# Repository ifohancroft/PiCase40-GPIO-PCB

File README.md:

Pi Case 40 GPIO PCB
===================

A replacement PCB (and a GPIO sticker) for the Pi Case 40, that fixes the reversed GPIO Issue.

 - The PCB can be located under PiCase40/. It includes all the schematic symbols, footprints and 3D shapes it uses, in project-specific libraries, located under Library/.
 - sticker.svg is the GPIO sticker.
 - PCBReference.FCStd contains the PCB dimensions and component placements, as well as technical drawings for all the important size and space restrictions that need to be taken into consideration when modifying the PCB or creating a new one.
 - TutorialDrawings/ contains the technical drawings from PCBReference.FCStd exported as png images, used later in the [Tutorial](#Tutorial) section.

## A small update - 13.02.2022

I am sorry for the enourmous delay, but I am not dead and neither is the project. In-fact, it's this close to a finished, ready to purchase sticker and a PCB.

- I have received a new sticker and I will test it tomorrow, but I have a feeling this one would fit. Then I'd update the README.

- I may have found a board house that can print and assemble the PCB. Ideally, if they can suggest a way the sandwitched PCB isn't needed, it would be even better. I will update as soon as I have anything concrete.

Table of contents
=================

<!--ts-->
   * [Pi Case 40 GPIO PCB](#pi-case-40-gpio-pcb)
   * [Table of contents](#table-of-contents)
   * [TODO](#todo)
      * [PCB TODO](#pcb-todo)
      * [Sticker TODO](#sticker-todo)
   * [Placing an order](#placing-an-order)
      * [Order a PCB](#order-a-pcb)
      * [Order a Sticker](#order-a-sticker)
   * [Modifying](#modifying)
      * [Modifying the PCB](#modifying-the-pcb)
      * [Modifying the Sticker](#modifying-the-sticker)
   * [Created with Free Software](#created-with-free-software)
   * [LICENSE](#license)
   * [Support my work](#support-my-work)
   * [Community repo](#community-repo)
<!--te-->

TODO
====

PCB TODO
--------

- Wait to hear back from the board house and go from there.

Sticker TODO
-------

1. Test the new sticker
2. Update the README appropriately, depending on whether the sticker fits or not.

Placing an order
================

Order a PCB
-----------

Order a Sticker
---------------

Modifying
========

Modifying the PCB
-----------------

In-case you want to modify this PCB, or create a new one from scratch, there are certain important dimensions you must know about:

As you can see, there are 4 different types of dimensions, marked in black, red, green and blue.

To make things easier to see, let's show each different type of dimensions on their own, when talking about them:

Black (Informative Dimentions) - You can't really change those, as they show typical component sizes, however some other dimensions may depend on them:

 - H: Width and Depth of the body of a typical tactile switch.
 - D: Depth of the body of a typical pin header (both male and female)
 - C: Width of the body of a typical pin header (both male and female)
 - V: V is an exception, as it doesn't show a component's dimension, instead it shows how far the vertical center of the male header is, from the grid's 0,0. This is to help you center everything.

Red (Exact Dimensions) - Dimensions that must be exactly as shown, or things won't fit:

 - B: Horizontal center to center distance of the mount holes - 58mm. Same as the center to center distance of the Raspberry Pi 4 mount holes and Pi 40 Case mount posts.
 - F: Horizontal center to center distance between the mount holes and the female pin header - 29mm.
 - I: Vertical center to center distance between the left mount hole and the tactile switch body - 7.5mm.
 - L: Vertical center to center distance between the tactile switch body and the top mount hole - 5mm.
 - K: Horizontal center to center distance between the tactile switch body and the top mount hole - 7mm.
 - G: Vertical center to center distance between the female and male pin headers - 7mm.

Blue (Restrictive Dimensions) - Dimensions that don't have to be as shown, but still have a limit as they depend on other dimentions and component placements:

 - A: Main mount holes diameter - 4mm. Must be between 4mm (bottom case mount posts' inner diameter) and 6mm (bottom case mount posts' outer diameter), so the PCB rests on the the posts, but allows the raised lip around the screw holes to go through.
 - E: Female header center to bottom board edge - 5mm. Must be between 5mm (half the thickness of a typical female pin header (dimension D:) + about 2.5mm for its SMD pads and some wiggle room) and 7mm as the inner board wall is 7mm away.
 - J: Top mount post hole diameter - 3mm. Must be less than 6mm (top mount post diameter) and not less than 2.5mm (top mount post inner diameter/screw hole diameter), so the PCB rests on the post but allows for the screw to go through.
 - O: Right mount hole center to board edge above it - 3.5mm. Must be bigger than half of dimension A to allow for some lip around the whole and not more than 3.54mm as Raspberry Pi's PoE header starts 3.54mm above the right screw hole center
 - P: Space for Pi's PoE Header - 3mm. Must be at least 2.6mm as the Pi's PoE header is 5.2mm by 5.2mm square on the same vertical axis as the right mount hole, but small enough to allow some lip around the male header for traces.
 - R: Cosmetic board cutout width - 5mm. If you are going to have this cutout, it must be at least as big as dimension M and less than K - J / 2 to allow for some lip to the left of both the tactile switch body and the top screw hole.
 - U: Case radiator support clearance - 6mm. It must be more than half of J to allow for some lip around the screw hole and depending on the degrees of the angle, watch out for the radiator support. Same X axis as the mount hole, 7mm to the right from its center the radiator support is reaches the height at which the PCB is mounted.
 - S: Male header center to top board edge - 4.5mm. It must be more than half of D to allow for some lip around the header, but not more than 4.5mm as the radiator starts about 4.5mm above where the center of your male header would be.
 - N: Right mount hole center to right board edge - 4mm. It must be more than half of A, to allow for some lip around the screw hole, but not more than 4.95mm as the Pi's Ethernet port starts there. Warning: If not the same as M, it would shift your board's horizontal center, making it difficult to center the board and position components relative to the center, without you having to find the new one yourself.
 - M: Left mount center center to left board edge - 4mm. It must be more than half of A, to allow for some lip around the screw hole, but not more than 5mm as this is where the inside of the left case wall starts. Warning: If not the same as N, it would shift your board's horizontal center, making it difficult to center the board and position components relative to the center, without you having to find the new one yourself.

Green (Loose Dimensions) - Dimensions that you can set to whatever you like (within reason) as every board edge or Pi component that is tall enough to interfere, are at least a couple of cm away:

 - Q: Button center to top board edge - 5.5mm. As long as it's big enough to leave some lip around the switch body for its SMD pads, you can have it couple of cm if you like.
 - T: Top mount hole center to top board edge - 2.5mm. As long as you leave some lip around the hole, you can have it couple of cm if you want, but if you have the slanted edge on the right, keep in mind U.

All corners are 135 degrees, and the length of all of them except for the two on top around the top mount hole is 1.5mm.

Modifying the sticker
---------------------

Created with Free Software
==========================

Everything has been created with [Free Software](https://www.gnu.org/philosophy/free-sw.en.html).

 - The PCB has been created with [KiCAD](https://kicad.org/) and [FreeCAD](https://www.freecadweb.org/) + the [KiCad StepUp Workbench](https://github.com/easyw/kicadStepUpMod)
 - PCBReference.FCStd has been created with [FreeCAD](https://www.freecadweb.org/)
 - The Sticker has been created with [Inkscape](https://inkscape.org/)
 - The README has been written with [Vim](https://www.vim.org/)

LICENSE
=======

Unless otherwise noted, everything is released under [CERN Open Hardware Licence Version 2 - Strongly Reciprocal](https://ohwr.org/project/cernohl/wikis/Documents/CERN-OHL-version-2).

Support my work
===============

If you find this project useful, please, consider supporting my work, using the Sponsor button in the top right.

Community repo
==============

Don't forget to check the community repo over at [https://github.com/Pi-Case-40-Community/PiCase40](https://github.com/Pi-Case-40-Community/PiCase40) that contains the community's creations for the Pi Case 40.

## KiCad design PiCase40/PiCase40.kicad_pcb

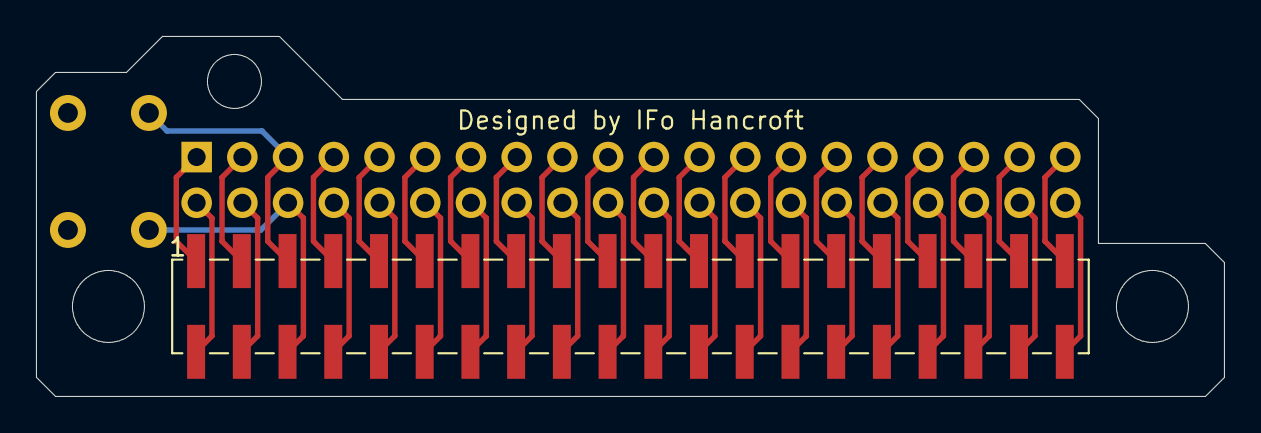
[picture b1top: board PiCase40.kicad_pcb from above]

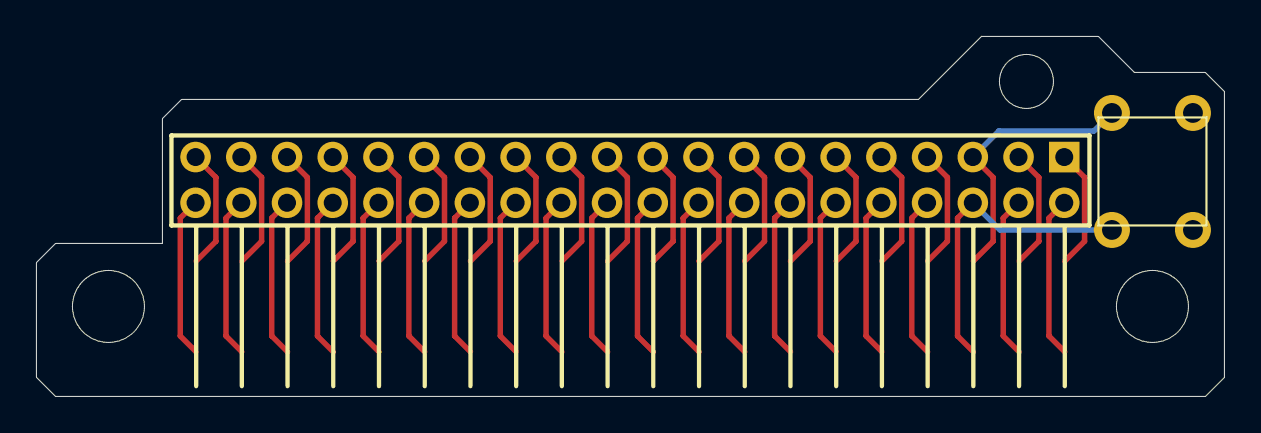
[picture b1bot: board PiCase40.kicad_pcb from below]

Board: 2 copper layers, 66.0 x 20.0 mm, 3 parts (2 on the bottom side), 2 nets.

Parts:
J1: Conn_02x20_Odd_Even_Male; PinHeader_2x20_P2.54mm_Horizontal
J2: Conn_02x20_Odd_Even_Female; PinSocket_2x20_P2.54mm_Vertical_SMD
SW1: SW_MEC_5E; SW_PUSH_6mm_H13mm

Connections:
/5: J1.5, SW1.1
/6: J1.6, SW1.3

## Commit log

2021-01-14 Initializing the repo with what I have so far
2021-01-16 Moved things around a bit
2021-01-16 Moved things around a bit. Again.
2021-01-19 Create FUNDING.yml
    Setting up my FUNDING.yml file.
2021-01-27 Changing the LICENSE to Attribution-NonCommercial-ShareAlike 4.0 International (CC BY-NC-SA 4.0), just to be on the safe side as Cooler Master has released the files for the Pi Case 40 and this the l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
2021-01-27 Editing the readme
2021-01-27 Revert "Changing the LICENSE to Attribution-NonCommercial-ShareAlike 4.0 International (CC BY-NC-SA 4.0), just to be on the safe side as Cooler Master has released the files for the Pi Case 40 and th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
    This reverts commit bb5b18ccf5d3e34108d255c4e6dc873d304fbc87.
2021-01-27 Revert "Editing the readme"
    This reverts commit 9d82b77d7abdff3ca16637b19a8089eaf6f39df2.
2021-01-27 Moved the technical drawings under Images/
2021-01-27 Renamed Images/ to Technical Drawings/
2021-01-27 Fixed a broken link in the README
2021-01-27 Fixing the folder name
2021-01-27 Adding dimensions
2021-01-27 Fixed a typo in the README
2021-01-27 Removed useless tabbing
2021-01-27 Testing something
2021-01-27 Adding dimensions info
2021-01-27 Finished adding dimensions
2021-01-27 Updating the TODO
2021-01-27 Fixed the LICENSE
2021-01-27 Removed duplicated section from the README
2021-02-04 Added an extra line to the README so I can test something
2021-02-04 Test
2021-02-04 New test
2021-02-13 Updated the PCB outline and pretified the footprints
2021-02-13 Updated the TODO section of the README and overall prettified the README
2021-02-13 Labeled the guide below as a Tutorial section
2021-02-13 Updated the README a bit
2021-02-13 Just testing something
2021-02-13 Updated the README
2021-02-13 Changed #2 in the TODO list from Buy a Raspberry to test to Buy a Raspberry and a HAT to test
2021-02-16 Prettified the PCB
2021-02-16 Added the gerbers that I have used to test the current the iteration
2021-02-16 Moved the FUNDING.yml to the root of the repo, as apparently that works
2021-02-16 Added a .gitignore to ignore zip files
2021-02-16 Updated the TODO to reflect the current state of the project
2021-02-16 Added a step to the TODO
2021-02-16 Added the files for the replacement sticker
2021-02-16 Added order instructions for the stickers, in the README
2021-02-16 Fixed a grammar error in the README
2021-02-16 Linked StickerMule's name to their website in the README
2021-02-16 Added license info to the README
2021-03-21 Deleted the PNG as it creates problems when printed
2021-03-22 Modified the sticker
2021-03-22 Removed multisticker as it won't be needed
2021-03-23 Prettyfing the repo and the README
2021-03-23 Prettifying the README
2021-04-01 Changed the sticker
2021-04-05 Added updates to the README
2021-07-16 Test is done
2022-02-13 Added a couple of updates to the README
